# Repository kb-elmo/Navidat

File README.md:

# Navidat

[![CC BY-NC-SA 4.0][cc-by-nc-sa-shield]][cc-by-nc-sa]

### Full navigation keypad

---

[STEP files for the case](case/)

[KiCAD PCB files](pcb/)

[Gerbers for PCB production](pcb/gerbers/)

[JLCPCB BOM](pcb/fab/navidat_bom_jlc.csv)

[JLCPCB CPL](pcb/fab/navidat_cpl_jlc.csv)

[Vial-QMK firmware](firmware/)

---

This work is licensed under a
[Creative Commons Attribution-NonCommercial-ShareAlike 4.0 International License][cc-by-nc-sa].

[![CC BY-NC-SA 4.0][cc-by-nc-sa-image]][cc-by-nc-sa]

[cc-by-nc-sa]: http://creativecommons.org/licenses/by-nc-sa/4.0/
[cc-by-nc-sa-image]: https://licensebuttons.net/l/by-nc-sa/4.0/88x31.png
[cc-by-nc-sa-shield]: https://img.shields.io/badge/License-CC%20BY--NC--SA%204.0-lightgrey.svg

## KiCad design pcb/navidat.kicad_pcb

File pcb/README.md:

# Navidat PCB

### Features

- Powered by an Atmega32u2
- Basic ESD and overvoltage protection
- Centered USB type-C port for a detachable cable
- Fully programmable using [QMK](https://qmk.fm) and [Vial](https://get.vial.today)

---

### Preview

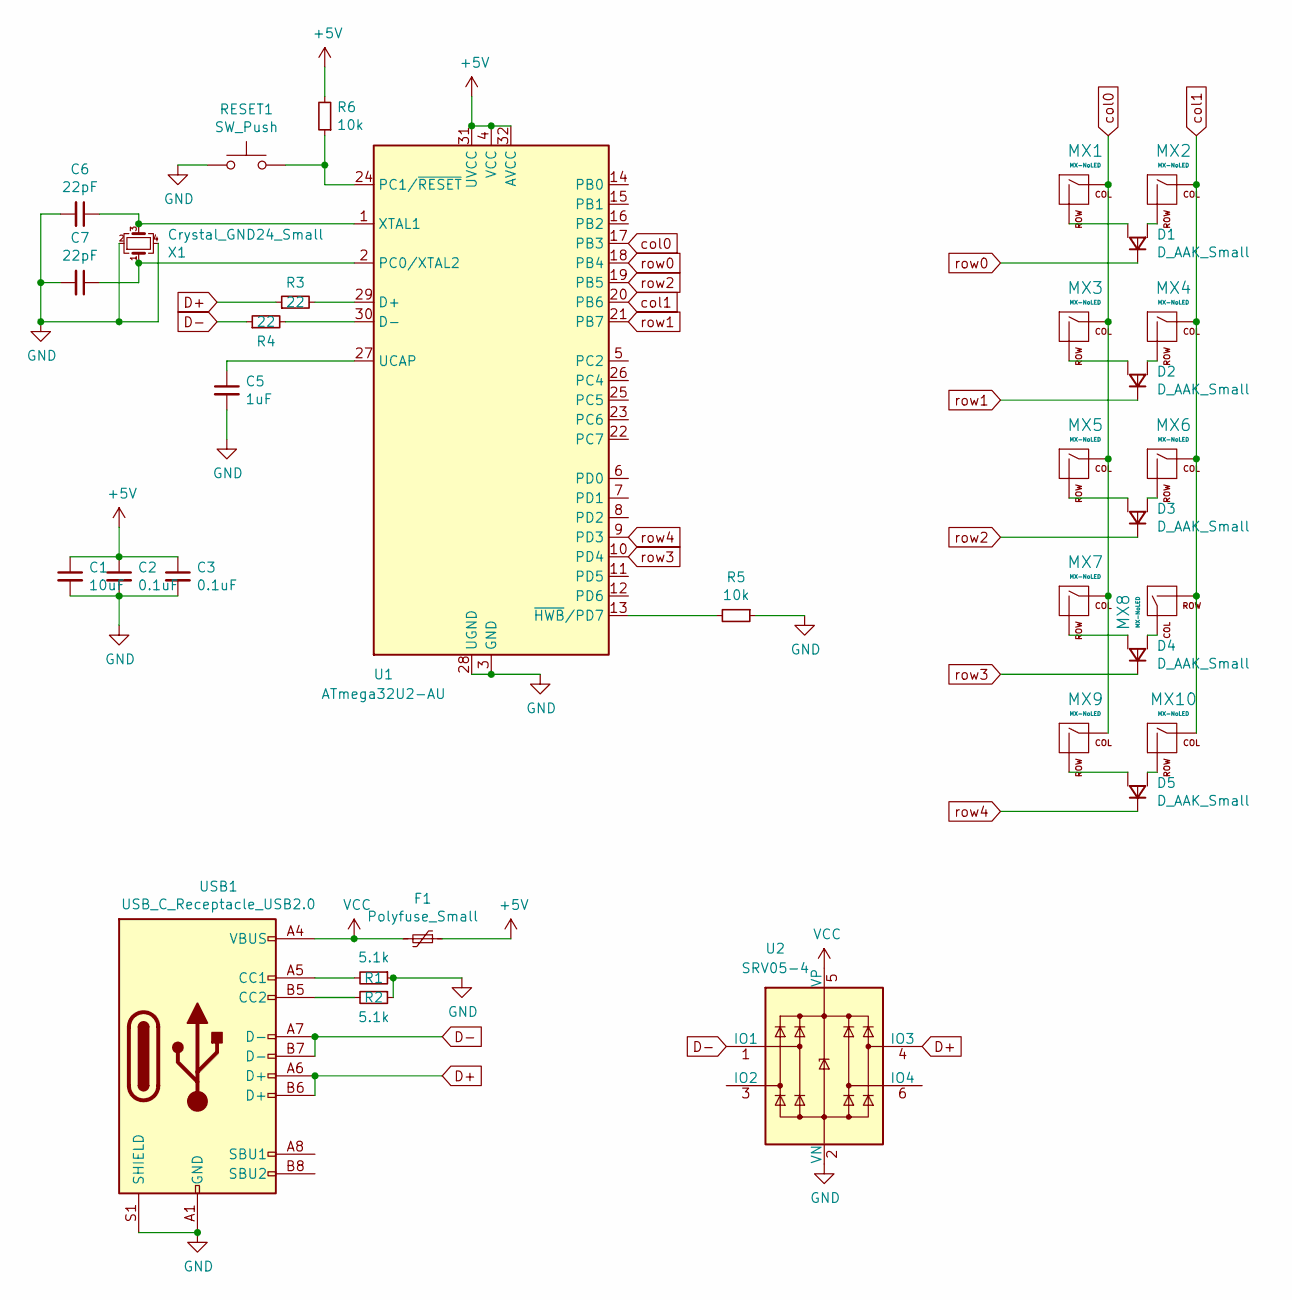
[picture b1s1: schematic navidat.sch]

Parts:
C1: 10uF; C_0805_2012Metric; LCSC C91245
C2, C3: 0.1uF; C_0805_2012Metric; LCSC C49678
C5: 1uF; C_0805_2012Metric; LCSC C28323
C6, C7: 22pF; C_0805_2012Metric; LCSC C1804
D1, D2, D3, D4, D5: D_AAK_Small; D_SOT-23_ANK_norm; LCSC C68978
F1: Polyfuse_Small; Fuse_1206_3216Metric; LCSC C69688
MX1, MX2, MX3, MX4, MX5, MX6, MX7, MX8, MX9, MX10: MX-NoLED; MXOnly-1U-NoLED
R1, R2: 5.1k; R_0805_2012Metric; LCSC C27834
R3, R4: 22; R_0805_2012Metric; LCSC C17561
R5, R6: 10k; R_0805_2012Metric; LCSC C17414
RESET1: SW_Push; SW_SPST_TL3342; LCSC C318884
U1: ATmega32U2-AU; TQFP-32_7x7mm_P0.8mm; LCSC C618733
U2: SRV05-4; SOT-23-6; LCSC C85364
USB1: USB_C_Receptacle_USB2.0; USB_C_Receptacle_HRO_TYPE-C-31-M-12; LCSC C165948
X1: Crystal_GND24_Small; Crystal_SMD_3225-4Pin_3.2x2.5mm; LCSC C13738

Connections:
+5V: C1.1, C2.1, C3.1, F1.1, R6.2, U1.4 (VCC), U1.31 (UVCC), U1.32 (AVCC)
D+: R3.1, U2.4 (IO3), USB1.A6 (D+), USB1.B6 (D+)
D-: R4.1, U2.1 (IO1), USB1.A7 (D-), USB1.B7 (D-)
GND: C1.2, C2.2, C3.2, C5.2, C6.2, C7.2, R1.1, R2.1, R5.1, RESET1.1, U1.3 (GND), U1.28 (UGND), U2.2 (VN), USB1.A1 (GND), USB1.A12 (GND), USB1.B1 (GND), USB1.B12 (GND), USB1.S1 (SHIELD), X1.2, X1.4; also elsewhere on the board
unnamed: C5.1, U1.27 (UCAP)
unnamed: C6.1, U1.1 (XTAL1), X1.3
unnamed: C7.1, U1.2 (PC0/XTAL2), X1.1
unnamed: D1.2 (A1), MX1.2 (ROW)
unnamed: D1.3 (A2), MX2.2 (ROW)
unnamed: D2.2 (A1), MX3.2 (ROW)
unnamed: D2.3 (A2), MX4.2 (ROW)
unnamed: D3.2 (A1), MX5.2 (ROW)
unnamed: D3.3 (A2), MX6.2 (ROW)
unnamed: D4.2 (A1), MX8.1 (COL)
unnamed: D4.3 (A2), MX7.2 (ROW)
unnamed: D5.2 (A1), MX10.2 (ROW)
unnamed: D5.3 (A2), MX9.2 (ROW)
unnamed: R1.2, USB1.A5 (CC1)
unnamed: R2.2, USB1.B5 (CC2)
unnamed: R3.2, U1.29 (D+)
unnamed: R4.2, U1.30 (D-)
unnamed: R5.2, U1.13 (~HWB~/PD7)
unnamed 22: R6.1, RESET1.2, U1.24 (PC1/~RESET); also elsewhere on the board
VCC: F1.2, U2.5 (VP), USB1.A4 (VBUS), USB1.A9 (VBUS), USB1.B4 (VBUS), USB1.B9 (VBUS)
col0: MX1.1 (COL), MX3.1 (COL), MX5.1 (COL), MX7.1 (COL), MX9.1 (COL), U1.17 (PB3)
col1: MX2.1 (COL), MX4.1 (COL), MX6.1 (COL), MX8.2 (ROW), MX10.1 (COL), U1.20 (PB6)
row0: D1.1 (K), U1.18 (PB4)
row1: D2.1 (K), U1.21 (PB7)
row2: D3.1 (K), U1.19 (PB5)
row3: D4.1 (K), U1.10 (PD4)
row4: D5.1 (K), U1.9 (PD3)

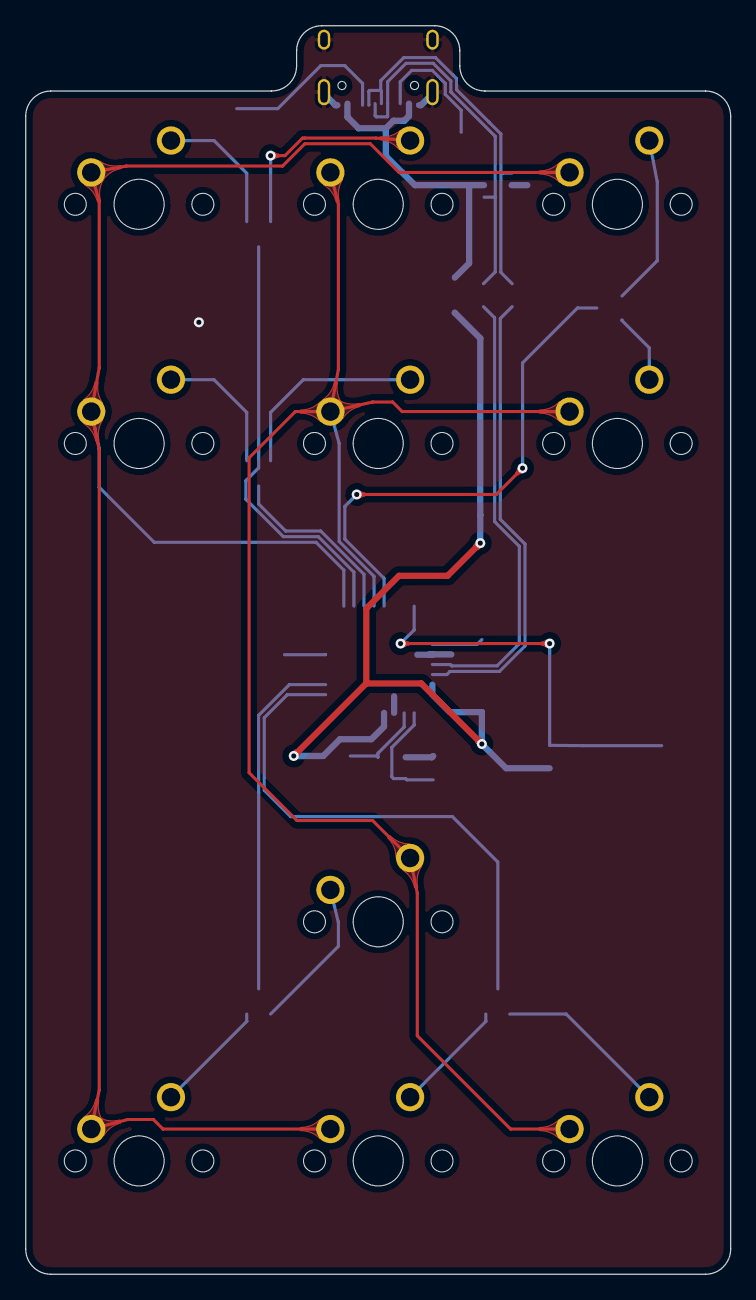
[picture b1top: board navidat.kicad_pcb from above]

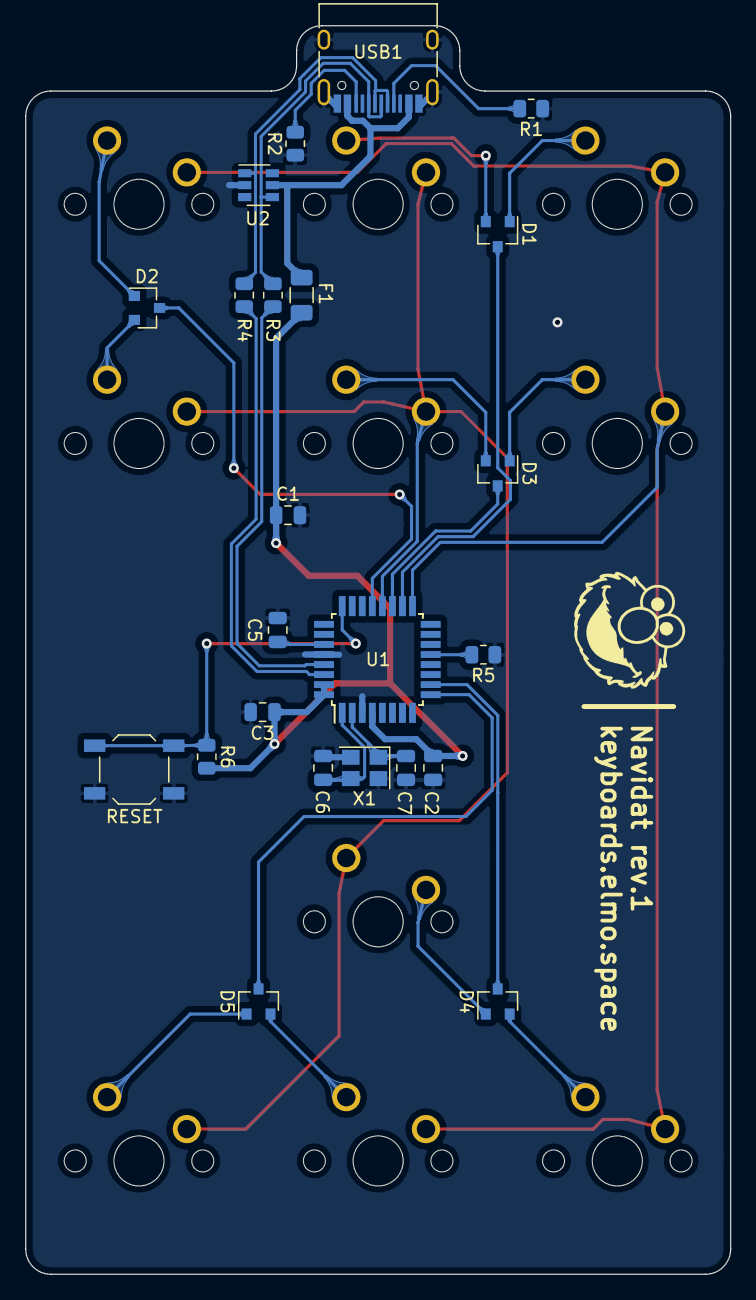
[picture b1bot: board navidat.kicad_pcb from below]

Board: 2 copper layers, 56.2 x 99.5 mm, 33 parts (23 on the bottom side), 31 nets.

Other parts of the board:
RESET: SW_Push; SW_SPST_TL3342

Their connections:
GND: RESET.1; also elsewhere on the board
unnamed 22: RESET.2; also elsewhere on the board

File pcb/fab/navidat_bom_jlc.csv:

"Comment","Designator","Footprint","LCSC Part #"
"10uF","C1","C_0805_2012Metric","C91245"
"0.1uF","C2,C3","C_0805_2012Metric","C49678"
"1uF","C5","C_0805_2012Metric","C28323"
"22pF","C6,C7","C_0805_2012Metric","C1804"
"D_AAK_Small","D1,D2,D3,D4,D5","D_SOT-23_ANK_norm","C68978"
"Polyfuse_Small","F1","Fuse_1206_3216Metric","C69688"
"5.1k","R1,R2","R_0805_2012Metric","C27834"
"22","R3,R4","R_0805_2012Metric","C17561"
"10k","R5,R6","R_0805_2012Metric","C17414"
"SW_Push","RESET1","SW_SPST_TL3342","C318884"
"ATmega32U2-AU","U1","TQFP-32_7x7mm_P0.8mm","C618733"
"SRV05-4","U2","SOT-23-6","C85364"
"USB_C_Receptacle_USB2.0","USB1","USB_C_Receptacle_HRO_TYPE-C-31-M-12","C165948"
"Crystal_GND24_Small","X1","Crystal_SMD_3225-4Pin_3.2x2.5mm","C13738"

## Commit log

2021-11-11 add image
2021-11-11 update PCB
2021-11-12 add firmware
2021-11-12 fix controller
